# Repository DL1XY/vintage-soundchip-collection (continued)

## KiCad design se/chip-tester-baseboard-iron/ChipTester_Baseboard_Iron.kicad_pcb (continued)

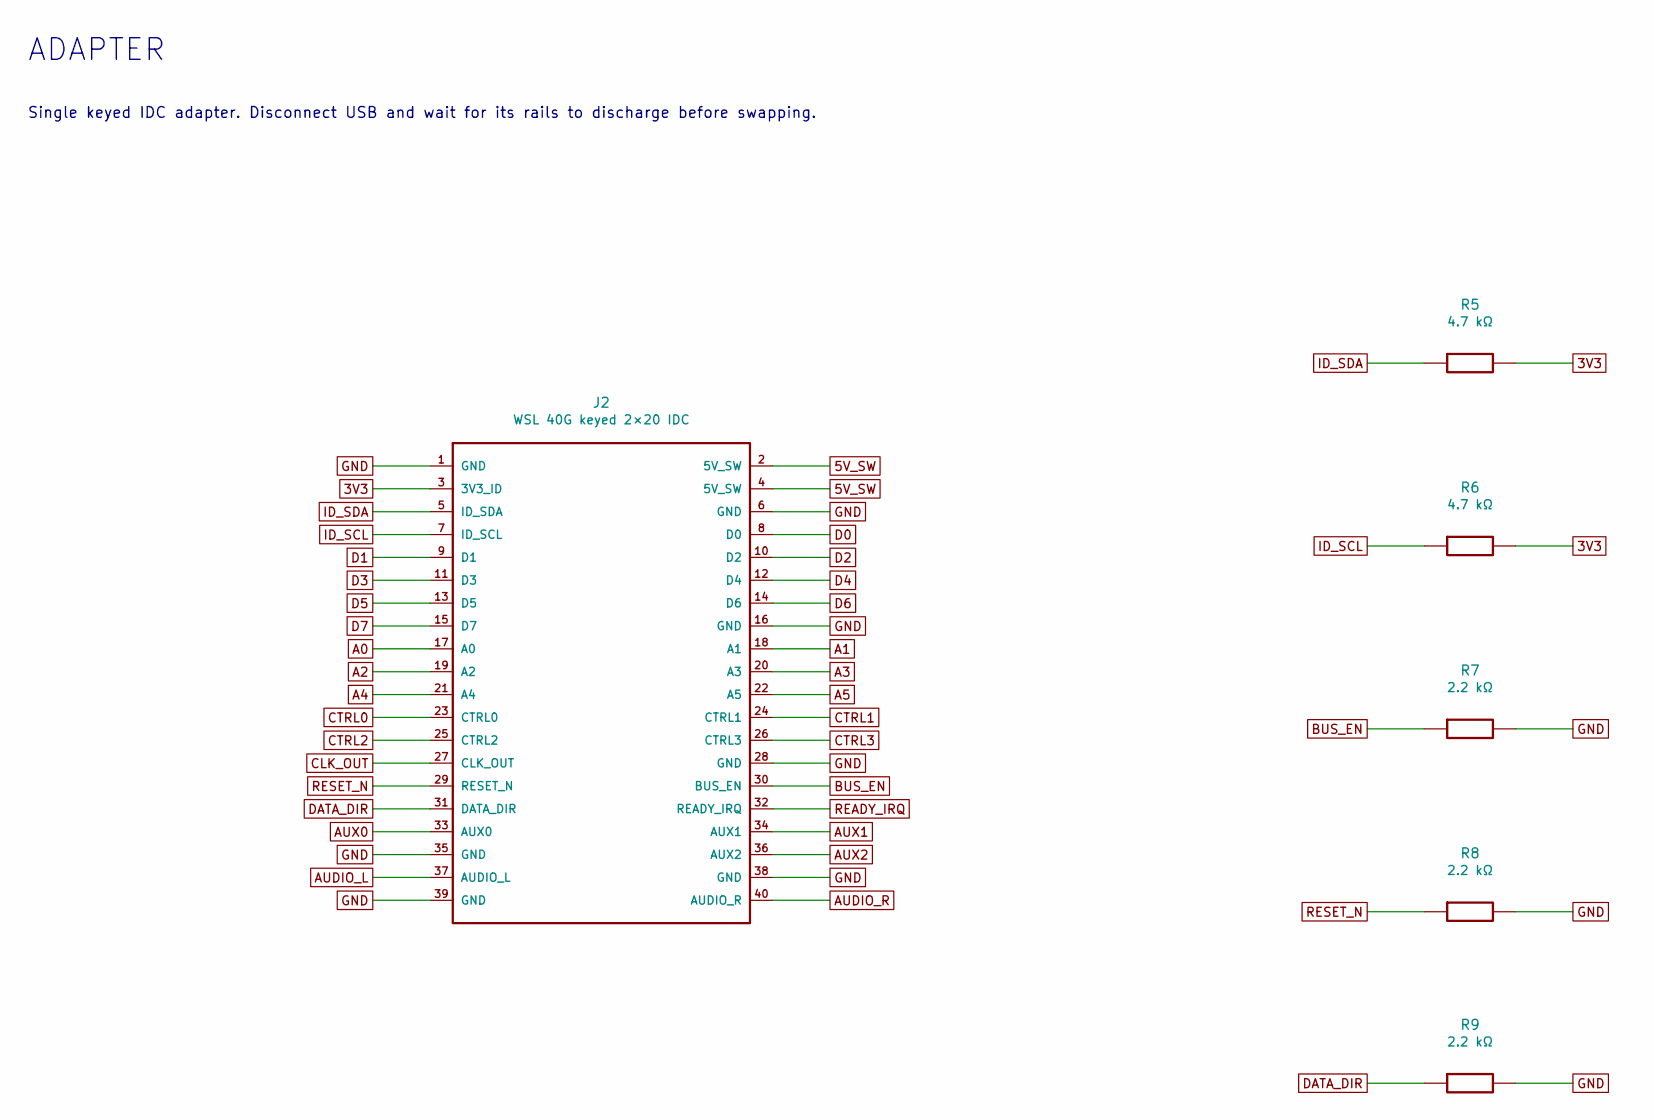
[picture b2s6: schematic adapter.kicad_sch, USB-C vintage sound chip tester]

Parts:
J2: WSL 40G keyed 2×20 IDC; IDC_2x20
R5, R6: 4.7 kΩ; Axial_7.62mm
R7, R8, R9: 2.2 kΩ; Axial_7.62mm

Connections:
3V3: J2.3 (3V3_ID), R5.2, R6.2; also elsewhere on the board
5V_SW: J2.2 (5V_SW), J2.4 (5V_SW); also elsewhere on the board
A0: J2.17 (A0); also elsewhere on the board
A1: J2.18 (A1); also elsewhere on the board
A2: J2.19 (A2); also elsewhere on the board
A3: J2.20 (A3); also elsewhere on the board
A4: J2.21 (A4); also elsewhere on the board
A5: J2.22 (A5); also elsewhere on the board
AUDIO_L: J2.37 (AUDIO_L); also elsewhere on the board
AUDIO_R: J2.40 (AUDIO_R); also elsewhere on the board
AUX0: J2.33 (AUX0); also elsewhere on the board
AUX1: J2.34 (AUX1); also elsewhere on the board
AUX2: J2.36 (AUX2); also elsewhere on the board
BUS_EN: J2.30 (BUS_EN), R7.1; also elsewhere on the board
CLK_OUT: J2.27 (CLK_OUT); also elsewhere on the board
CTRL0: J2.23 (CTRL0); also elsewhere on the board
CTRL1: J2.24 (CTRL1); also elsewhere on the board
CTRL2: J2.25 (CTRL2); also elsewhere on the board
CTRL3: J2.26 (CTRL3); also elsewhere on the board
D0: J2.8 (D0); also elsewhere on the board
D1: J2.9 (D1); also elsewhere on the board
D2: J2.10 (D2); also elsewhere on the board
D3: J2.11 (D3); also elsewhere on the board
D4: J2.12 (D4); also elsewhere on the board
D5: J2.13 (D5); also elsewhere on the board
D6: J2.14 (D6); also elsewhere on the board
D7: J2.15 (D7); also elsewhere on the board
DATA_DIR: J2.31 (DATA_DIR), R9.1; also elsewhere on the board
GND: J2.1 (GND), J2.6 (GND), J2.16 (GND), J2.28 (GND), J2.35 (GND), J2.38 (GND), J2.39 (GND), R7.2, R8.2, R9.2; also elsewhere on the board
ID_SCL: J2.7 (ID_SCL), R6.1; also elsewhere on the board
ID_SDA: J2.5 (ID_SDA), R5.1; also elsewhere on the board
READY_IRQ: J2.32 (READY_IRQ); also elsewhere on the board
RESET_N: J2.29 (RESET_N), R8.1; also elsewhere on the board

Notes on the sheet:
Single keyed IDC adapter. Disconnect USB and wait for its rails to discharge before swapping.
ADAPTER

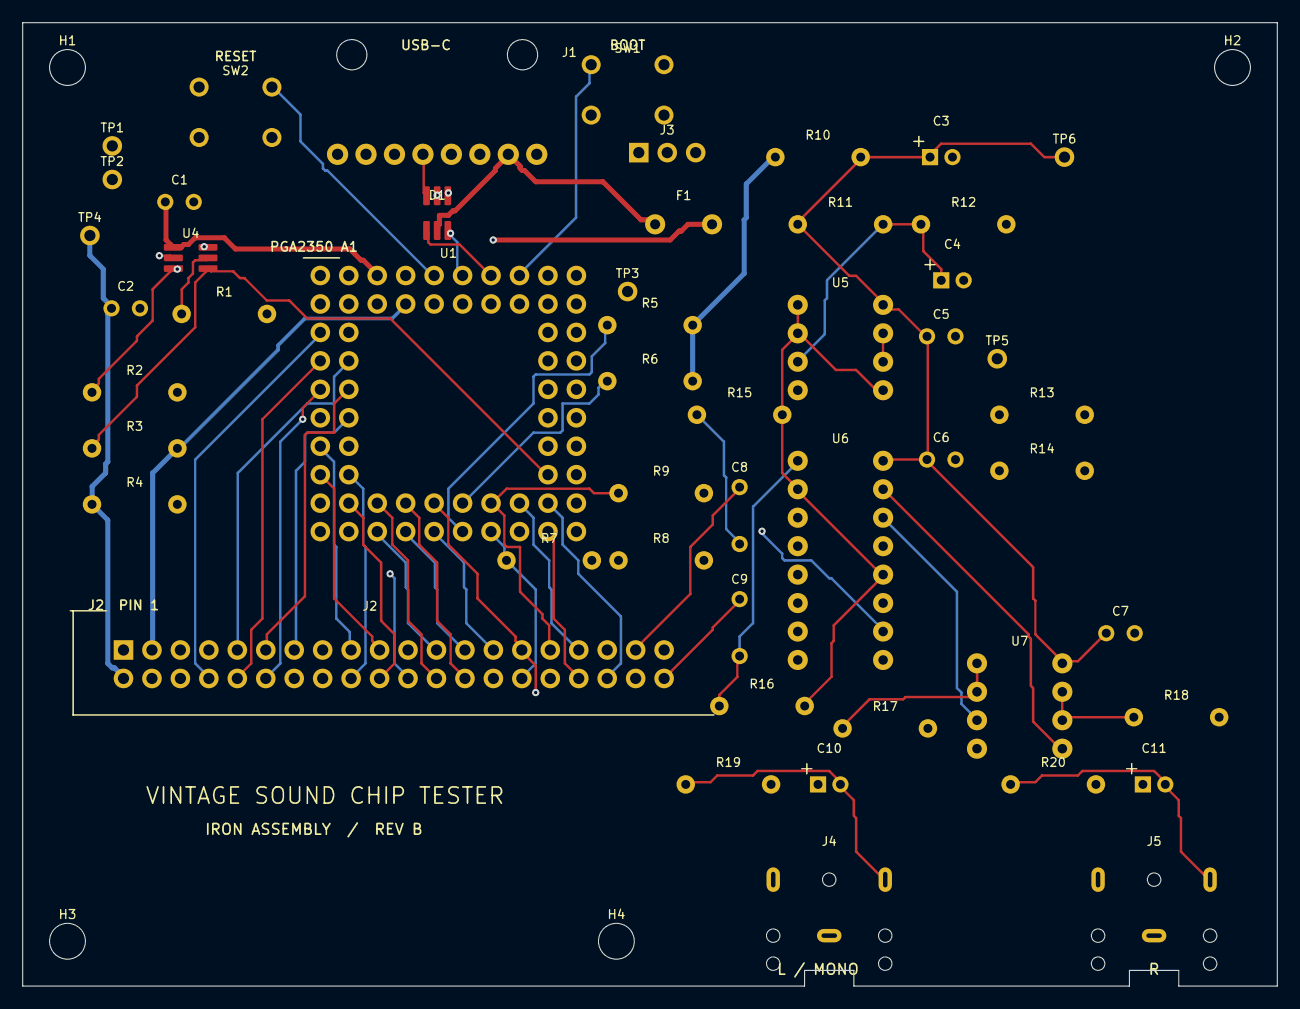
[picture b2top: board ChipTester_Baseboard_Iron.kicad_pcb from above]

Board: 4 copper layers, 112.0 x 86.0 mm, 55 parts (0 on the bottom side), 62 nets.

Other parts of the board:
H1, H2, H3, H4: M3; MountingHole_3.2mm
